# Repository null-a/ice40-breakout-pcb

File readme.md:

# Lattice iCE40 HX4K breakout / dev board

## Introduction

This KiCAD project contains the design of a break out / dev board for
a Lattice iCE40 HX4K FPGA.

I'm a novice at PCB design, so please don't assume anything here
represents good practice. I was motivated to tackle this after seeing
Matt Venn's [iCE40 board](https://github.com/mattvenn/first-fpga-pcb).
Some elements of the design are based on
the [TinyFPGA BX](https://github.com/tinyfpga/TinyFPGA-BX).

## Features

* SPI flash for configuration.
* On-board clock.
* Powered by 5v from a micro USB connector. Regulators for 3.3v and
  1.2v. Power LED.
* Single output LED.
* 72 GPIO pins broken out. sysCONFIG pins broken out for programming
  the flash. Cold boot config pins broken out.
* The USB data lines are connected to the FPGA. This makes it possible
  to program the board directly over USB using e.g. the TinyFPGA
  bootloader.
* 2 layer PCB.
* Designed for hand assembly.

## Project Log

* 2021-06-07: I now have the
  [TinyFPGA bootloader](https://github.com/tinyfpga/TinyFPGA-Bootloader) working.
* 2021-05-22: Confirmed that I can blink the on-board LED using the
  FPGA. I'm currently using an external programmer to load the
  configuration into the on-board flash. (See [blinky](blinky).)
* 2021-05-12: First
  board
  [assembled](https://www.dropbox.com/s/xi2ujczmzbuk978/?raw=1).
* 2021-05-10: Prototype boards received.
* 2021-04-22:
  [Revision A](https://www.dropbox.com/s/bwuf1rviyvo0iy6/?raw=1) of
  the board completed. Prototype boards ordered.

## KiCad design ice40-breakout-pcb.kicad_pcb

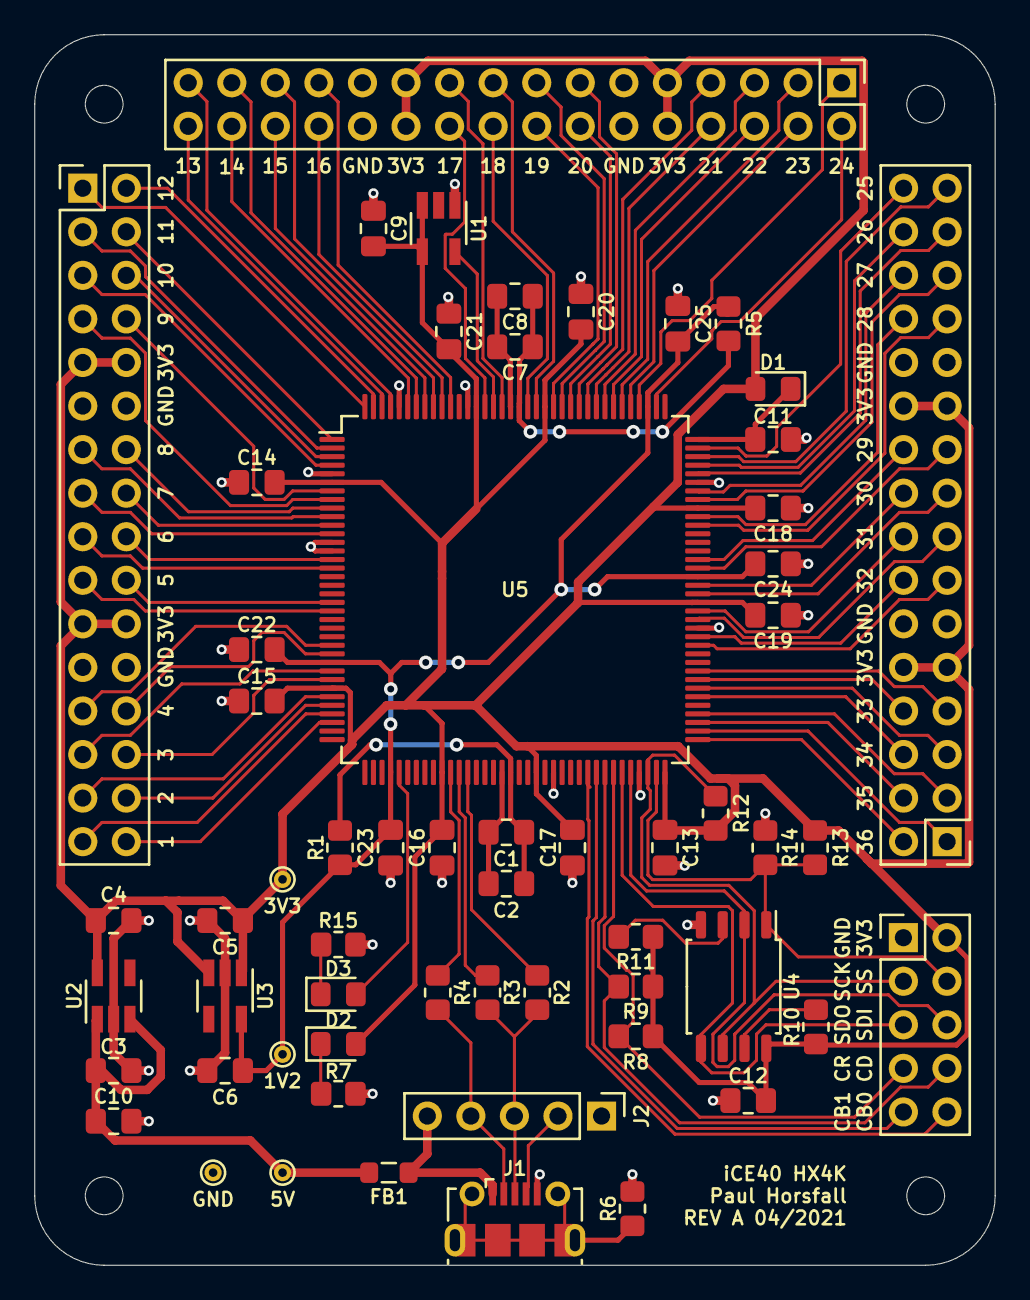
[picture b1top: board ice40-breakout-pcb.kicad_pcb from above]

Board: 2 copper layers, 56.0 x 71.8 mm, 59 parts (0 on the bottom side), 103 nets.

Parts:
C1, C7, C10: 10uF; C_0805_2012Metric_Pad1.18x1.45mm_HandSolder
C2, C8, C9, C11, C12, C13, C14, C15, C16, C17, C18, C19, C20, C21, C22, C23, C24, C25: 0.1uF; C_0805_2012Metric_Pad1.18x1.45mm_HandSolder
C3, C4, C5, C6: 1uF; C_0805_2012Metric_Pad1.18x1.45mm_HandSolder
D1: Short; D_0805_2012Metric_Pad1.15x1.40mm_HandSolder
D2, D3: LED; LED_0805_2012Metric_Pad1.15x1.40mm_HandSolder
FB1: 30 ohm; L_0805_2012Metric_Pad1.05x1.20mm_HandSolder
J1: USB_B_Micro; USB_Micro-B_Molex-105017-0001
J2: USB_Break_Out; PinHeader_1x05_P2.54mm_Vertical
J3, J4, J5: Conn_02x16_Odd_Even; PinHeader_2x16_P2.54mm_Vertical
J6: Conn_02x04_Odd_Even; PinHeader_2x05_P2.54mm_Vertical
R1, R5: 100; R_0805_2012Metric_Pad1.20x1.40mm_HandSolder
R2: 1.5K; R_0805_2012Metric_Pad1.20x1.40mm_HandSolder
R3, R4: 68; R_0805_2012Metric_Pad1.20x1.40mm_HandSolder
R6, R10, R11: 0; R_0805_2012Metric_Pad1.20x1.40mm_HandSolder
R7, R15: 330; R_0805_2012Metric_Pad1.20x1.40mm_HandSolder
R8, R9, R12, R13: 10K; R_0805_2012Metric_Pad1.20x1.40mm_HandSolder
R14: NP; R_0805_2012Metric_Pad1.20x1.40mm_HandSolder
TP1, TP2, TP3, TP4: TestPoint; TestPoint_THTPad_D1.0mm_Drill0.5mm
U1: SIT2001BI-S2-33E-12.000000G; SOT-23-5_HandSoldering
U2: TLV73333PDBV; SOT-23-5_HandSoldering
U3: TLV73312PDBV; SOT-23-5_HandSoldering
U4: AT25SF081-SHD-X; SOIC-8_5.23x5.23mm_P1.27mm
U5: ICE40HX4K-TQ144; TQFP-144_20x20mm_P0.5mm

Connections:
+1V2: C6.1, C22.2, C23.2, C24.2, C25.2, R1.1, R5.1, TP3.1, U3.5, U5.27, U5.40, U5.92, U5.111
+3V3: C4.1, C5.1, C9.2, C12.2, C13.1, C14.2, C15.2, C16.2, C17.2, C18.2, C19.2, C20.2, C21.2, D1.2, D2.2, J3.9, J3.10, J3.21, J3.22, J4.9, J4.10, J4.21, J4.22, J5.9, J5.10, J5.21, J5.22, J6.2, R8.1, R9.1, R10.1, R11.1, R12.1, R13.1, TP2.1, U1.3, U1.4, U2.5, U3.1, U3.3, U4.8, U5.6, U5.30, U5.46, U5.57, U5.72, U5.89, U5.100, U5.123, U5.131
+5V: C3.1, C10.1, FB1.2, TP1.1, U2.1, U2.3
CDONE: J6.8, R9.2, U5.65
CLK: U1.5, U5.129
CRESET: J6.7, R8.2, U5.66
GND: C3.2, C4.2, C5.2, C6.2, C9.1, C10.2, C11.2, C12.1, C13.2, C14.1, C15.1, C16.1, C17.1, C18.1, C19.1, C20.1, C21.1, C22.1, C23.1, C24.1, C25.1, J1.5, J2.1, J3.11, J3.12, J3.23, J3.24, J4.11, J4.12, J4.23, J4.24, J5.11, J5.12, J5.23, J5.24, J6.1, R6.2, R7.2, R14.1, R15.2, TP4.1, U1.1, U2.2, U3.2, U4.4, U5.5, U5.13, U5.14, U5.59, U5.69, U5.86, U5.103, U5.132, U5.140
GNDPLL0: C1.2, C2.2, U5.53
GNDPLL1: C7.2, C8.2, U5.127
LED: D3.2, U5.41
unnamed: D2.1, R7.1
unnamed: D3.1, R15.1
unnamed: FB1.1, J1.1, J2.5
unnamed: J1.2, J2.4, R4.2
unnamed: J1.3, J2.3, R2.2, R3.2
unnamed: J1.4, J2.2
unnamed: J1.6, R6.1
unnamed: R10.2, U4.7
unnamed: R11.2, U4.3
SPI_MISO: J6.6, U4.2, U5.68
SPI_MOSI: J6.5, U4.5, U5.67
SPI_SCK: J6.3, R12.2, U4.6, U5.70
SPI_SS: J6.4, R13.2, R14.2, U4.1, U5.71
USB_N: R4.1, U5.47
USB_P: R3.1, U5.48
USB_PU: R2.1, U5.49
VCCPLL0: C1.1, C2.1, R1.2, U5.54
VCCPLL1: C7.1, C8.1, R5.2, U5.126
VPP_2V5: C11.1, D1.1, U5.108
cbsel0: J6.10, U5.63
cbsel1: J6.9, U5.64
gp_a_1: J3.1, U5.144
gp_a_2: J3.2, U5.143
gp_a_3: J3.3, U5.2
gp_a_4: J3.4, U5.1
gp_a_5: J3.5, U5.4
gp_a_6: J3.6, U5.3
gp_a_7: J3.7, U5.8
gp_a_8: J3.8, U5.7
gp_a_9: J3.13, U5.10
gp_a_10: J3.14, U5.9
gp_a_11: J3.15, U5.12
gp_a_12: J3.16, U5.11
gp_a_13: J3.17, U5.16
gp_a_14: J3.18, U5.15
gp_a_15: J3.19, U5.21
gp_a_16: J3.20, U5.20
gp_a_17: J3.25, U5.25
gp_a_18: J3.26, U5.26
gp_a_19: J3.27, U5.28
gp_a_20: J3.28, U5.29
gp_a_21: J3.29, U5.31
gp_a_22: J3.30, U5.32
gp_a_23: J3.31, U5.33
gp_a_24: J3.32, U5.34
gp_b_1: J5.1, U5.112
gp_b_2: J5.2, U5.110
gp_b_3: J5.3, U5.114
gp_b_4: J5.4, U5.113
gp_b_5: J5.5, U5.116
gp_b_6: J5.6, U5.115
gp_b_7: J5.7, U5.118
gp_b_8: J5.8, U5.117
gp_b_9: J5.13, U5.119
gp_b_10: J5.14, U5.120
gp_b_11: J5.15, U5.121
gp_b_12: J5.16, U5.122
gp_b_13: J5.17, U5.124
gp_b_14: J5.18, U5.125
gp_b_15: J5.19, U5.128
gp_b_16: J5.20, U5.130
gp_b_17: J5.25, U5.134
gp_b_18: J5.26, U5.135
gp_b_19: J5.27, U5.136
gp_b_20: J5.28, U5.137
gp_b_21: J5.29, U5.138
gp_b_22: J5.30, U5.139
gp_b_23: J5.31, U5.141
gp_b_24: J5.32, U5.142
gp_c_1: J4.1, U5.74
gp_c_2: J4.2, U5.73
gp_c_3: J4.3, U5.76
gp_c_4: J4.4, U5.75
gp_c_5: J4.5, U5.79
gp_c_6: J4.6, U5.78
gp_c_7: J4.7, U5.81
gp_c_8: J4.8, U5.80
gp_c_9: J4.13, U5.84
gp_c_10: J4.14, U5.85
gp_c_11: J4.15, U5.87
gp_c_12: J4.16, U5.88
gp_c_13: J4.17, U5.90
gp_c_14: J4.18, U5.91
gp_c_15: J4.19, U5.93
gp_c_16: J4.20, U5.94
gp_c_17: J4.25, U5.98
gp_c_18: J4.26, U5.99
gp_c_19: J4.27, U5.101
gp_c_20: J4.28, U5.102
gp_c_21: J4.29, U5.104
gp_c_22: J4.30, U5.105
gp_c_23: J4.31, U5.106
gp_c_24: J4.32, U5.107

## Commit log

2021-04-16 First pass at schema entry.
2021-04-16 Initial component placement.
2021-04-16 Allocate FPGA pins for LED & USB.
2021-04-18 Make it easier to route PLL grounds.
2021-04-18 Re-position SCK pull-up to give SS a path to connector.
2021-04-18 Place cap next to power pin.
2021-04-18 Allocate FPGA pin for LED.
2021-04-18 Adjust component placement for easy soldering.
2021-04-19 Tweak board set-up. (Trace widths, etc.)
2021-04-19 First pass at routing for core.
2021-04-19 Experimenting with external connector configuration.
2021-04-19 Fine adjustment of board outline.
2021-04-19 Adjust power to make it easier to break out more signals.
2021-04-19 Cosmetic tweak.
2021-04-19 Move SPI connector to make room for mounting hole.
2021-04-20 Initial routing of GPIO.
2021-04-20 Reposition voltage regulators for more compact layout.
2021-04-20 Shorten the board.
2021-04-20 Experimental mounting hole in top-right.
2021-04-20 Re-jig bottom right of layout to put connector on edge of board.
2021-04-20 Bring CBSEL lines out to connector.
2021-04-20 Reduce board length to match length of connectors.
2021-04-20 Add remaining mounting holes.
2021-04-20 Make ERC pass in schematic.
2021-04-21 Route GBIN pins where possible.
2021-04-21 Make 3v3 power tracks wider in most places.
2021-04-21 Have LEDs orientated the same way.
2021-04-21 Fix-up USB routing.
2021-04-21 Add missing 3v3 route.
2021-04-21 Use wider trace for 3v3 power to external connector & add GND plane.
2021-04-21 Add ground vias.
2021-04-21 Connect USB socket pads to keep DRC happy.
2021-04-21 Fix-up front silk screen.
2021-04-21 Fix component spacing inline with rest of layout.
2021-04-21 Label main external connectors.
2021-04-21 Re-jig bottom right corner to accommodate labels.
2021-04-21 Label SPI connector.
2021-04-21 Fix wonky test point placement.
2021-04-21 Add name, date, revision, etc. to silk screen.
2021-04-21 Re-fill ground plane.
2021-04-22 Tweak silk screen text.
2021-04-22 Remove stale TODO note.
2021-04-22 Add missing component values.
2021-04-23 Add readme.
2021-05-11 Update readme.
2021-05-22 Tweak readme.
2021-05-22 Blinky.
2021-05-22 Link to images from the readme.
2021-06-07 Update project log.
